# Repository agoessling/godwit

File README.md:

godwit
======

Low-Cost Gliding Computer

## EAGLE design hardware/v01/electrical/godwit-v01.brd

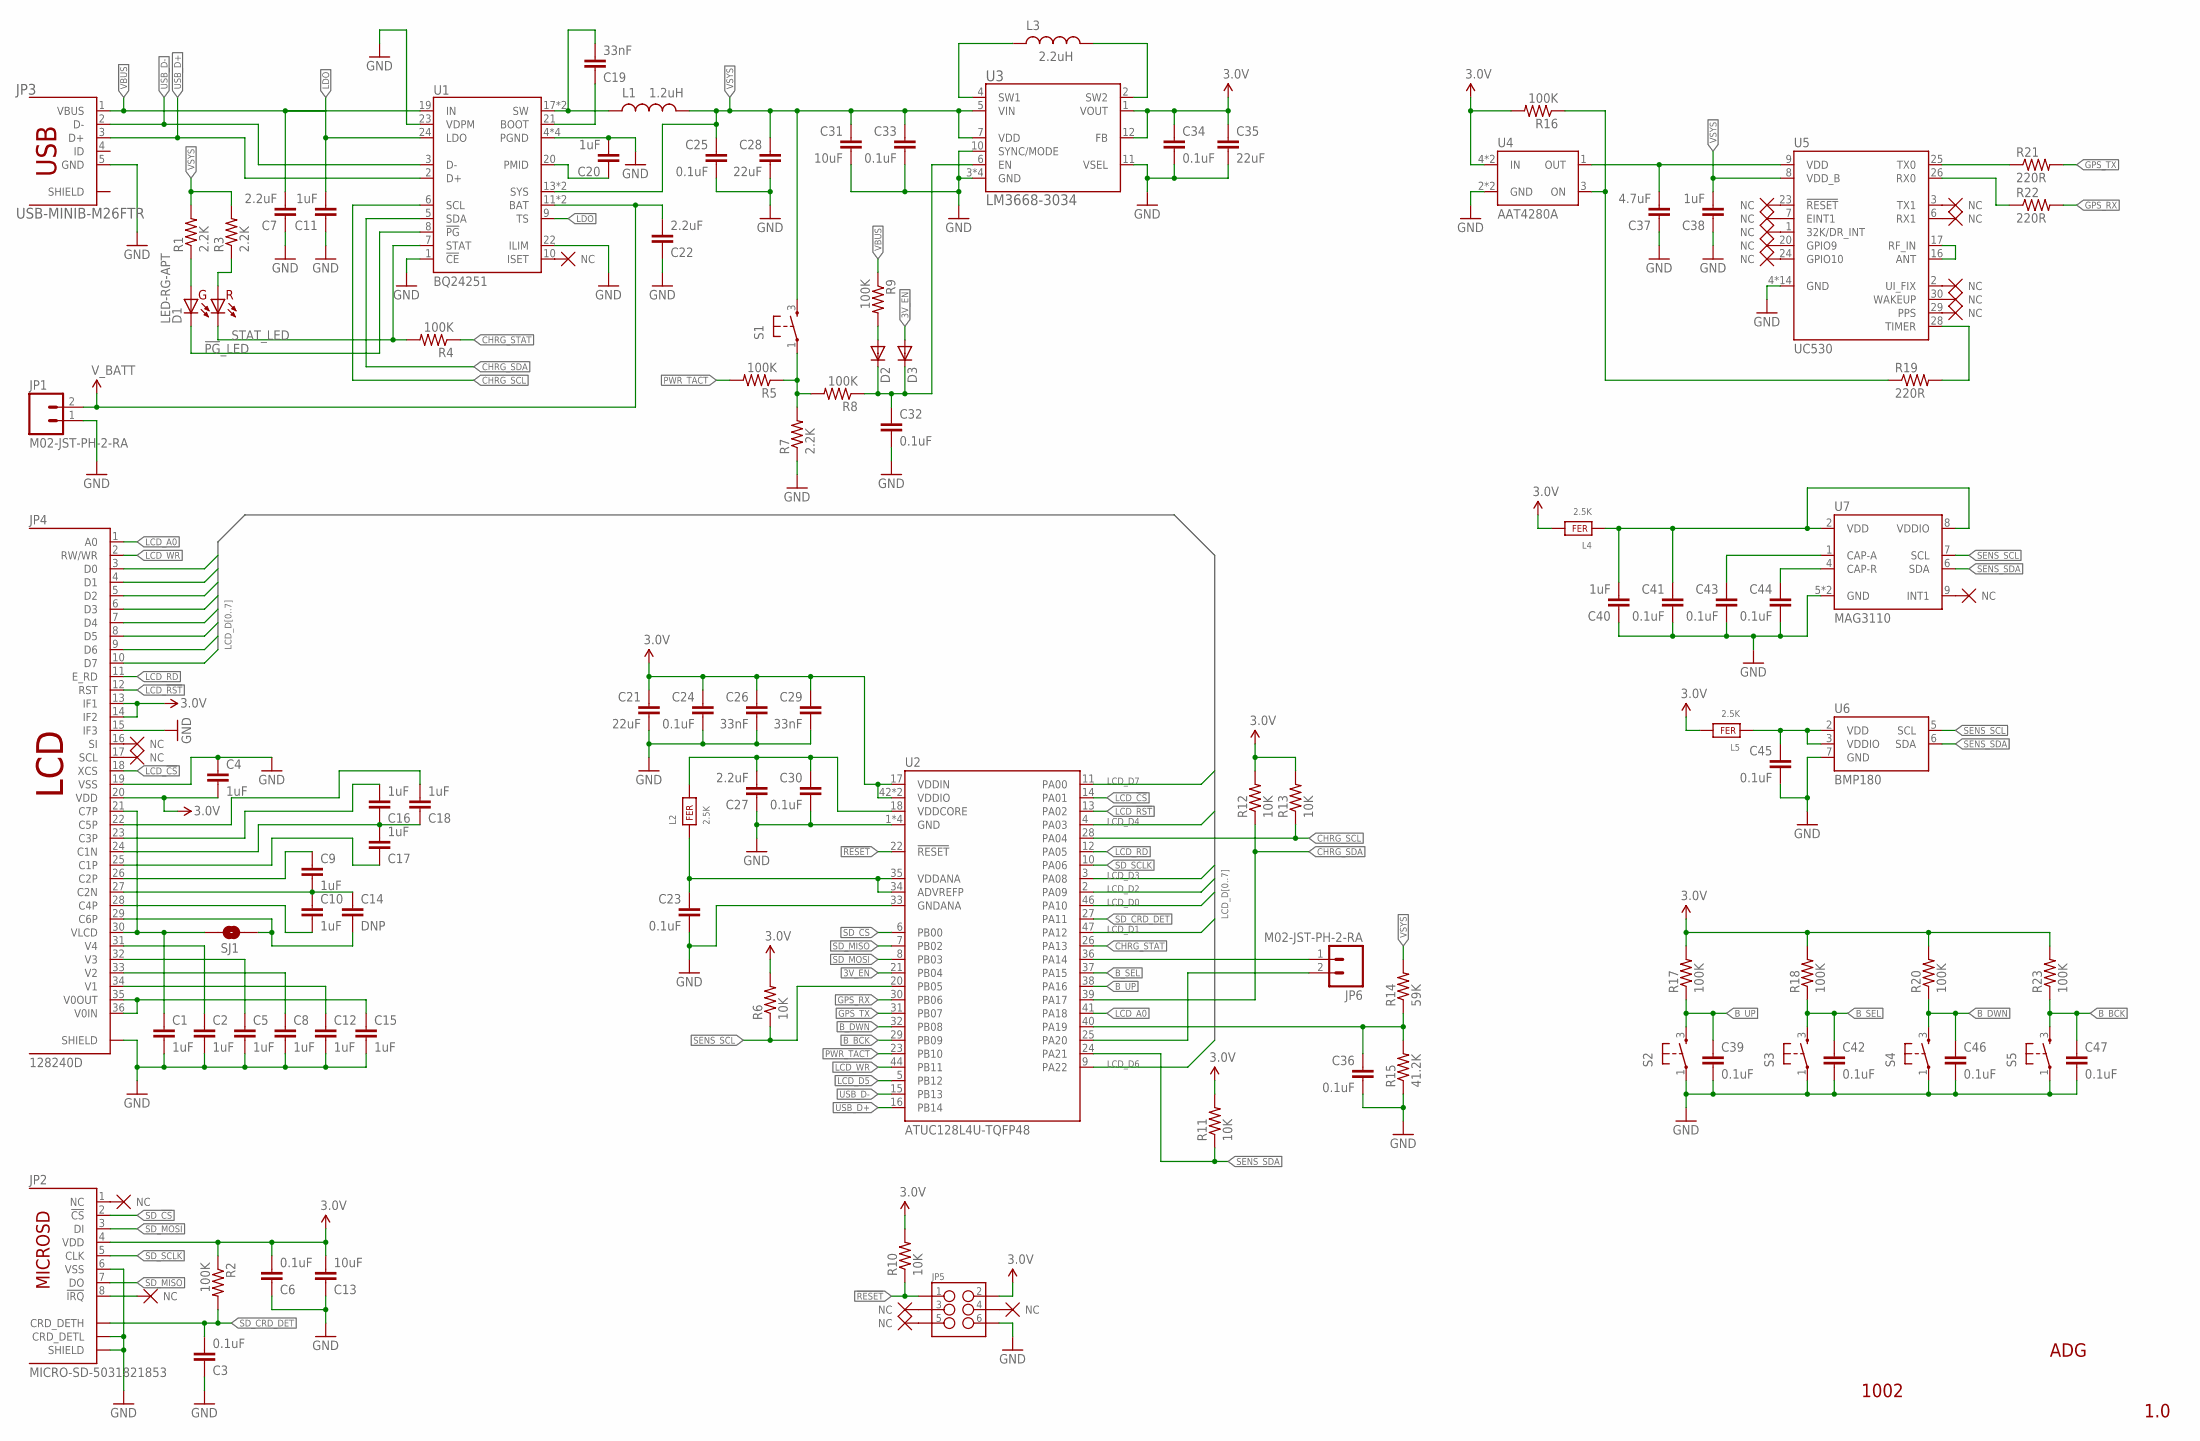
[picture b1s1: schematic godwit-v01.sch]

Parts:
C1, C2, C4, C5, C8, C9, C10, C12, C15, C16, C17, C18: 1uF; C0603
C3, C6, C23, C24, C25, C30, C32, C33, C34, C36, C39, C41, C42, C43, C44, C45, C46, C47: 0.1uF; C0603
C7, C22, C27: 2.2uF; C0603
C11, C20, C38, C40: 1uF; C0603; VOLTAGE >=10V
C13, C31: 10uF; C0805
C14: DNP; C0603
C19: 33nF; C0603; VOLTAGE >15
C21, C28, C35: 22uF; C0805
C26, C29: 33nF; C0603
C37: 4.7uF; C0603; VOLTAGE >=10V
D1: LED-RG-APT; LED-2-1.6X1.25
D2, D3: 1N4148X-TP; SOD523
JP1, JP6: M02-JST-PH-2-RA; JST-PH-2-RA
JP2: MICRO-SD-5031821853; MICROSD-5031821853
JP3: USB-MINIB-M26FTR
JP4: 128240D
JP5: M03X2NO_SILK; 2X3-NS
L1: 1.2uH; SRU5028
L2, L4, L5: 2.5K; 0603
L3: 2.2uH; SRU5028
R1, R3, R7: 2.2K; R0603
R2, R4, R5, R8, R9, R16, R17, R18, R20, R23: 100K; R0603
R6, R10, R11, R12, R13: 10K; R0603
R14: 59K; R0603
R15: 41.2K; R0603
R19, R21, R22: 220R; R0603
S1, S2, S3, S4, S5: FSMRA7JH; FSMRA
SJ1: SOLDERJUMPERNC; SJ_2S
U1: BQ24251; VQFN-24
U2: ATUC128L4U-TQFP48; TQFP48
U3: LM3668-3034; WSON-12
U4: AAT4280A; SOT23-6
U5: UC530
U6: BMP180
U7: MAG3110; DFN-10-2X2

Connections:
3.0V: C4.2, C6.2, C13.2, C21.1, C24.1, C26.1, C29.1, C34.1, C35.1, JP2.4 (VDD), JP4.13 (IF1), JP4.14 (IF2), JP4.20 (VDD), JP5.2, L4.2, L5.2, R2.1, R6.2, R10.2, R11.2, R12.2, R13.2, R16.2, R17.2, R18.2, R20.2, R23.2, U2.17 (VDDIN), U2.42 (VDDIO), U2.48 (VDDIO), U3.1 (VOUT), U3.12 (FB), U4.4 (IN), U4.6 (IN)
3V_EN: D3.A, U2.21 (PB04)
!PG!_LED: D1.4 (CG), U1.8 (!PG!)
!RESET!: JP5.1, R10.1, U2.22 (!RESET!)
B_BCK: C47.1, R23.1, S5.3 (2), U2.29 (PB09)
B_DWN: C46.1, R20.1, S4.3 (2), U2.32 (PB08)
B_SEL: C42.1, R18.1, S3.3 (2), U2.37 (PA15)
B_UP: C39.1, R17.1, S2.3 (2), U2.38 (PA16)
CHRG_SCL: R13.1, U1.6 (SCL), U2.28 (PA04)
CHRG_SDA: R12.1, U1.5 (SDA), U2.39 (PA17)
CHRG_STAT: R4.1, U2.26 (PA13)
GND: C1.2, C2.2, C3.1, C4.1, C5.2, C6.1, C7.1, C8.2, C11.1, C12.2, C13.1, C15.2, C20.2, C21.2, C22.1, C23.2, C24.2, C25.2, C26.2, C27.1, C28.2, C29.2, C30.2, C31.2, C32.2, C33.2, C34.2, C35.2, C36.2, C37.1, C38.1, C39.2, C40.1, C41.2, C42.2, C43.2, C44.2, C45.2, C46.2, C47.2, JP1.1, JP2.6 (VSS), JP2.CRD_DETL, JP2.SHIELD1 (SHIELD), JP2.SHIELD2 (SHIELD), JP2.SHIELD3 (SHIELD), JP2.SHIELD4 (SHIELD), JP2.SHIELD5 (SHIELD), JP3.5 (GND), JP4.15 (IF3), JP4.19 (VSS), JP4.SHIELD1 (SHIELD), JP4.SHIELD2 (SHIELD), JP5.6, R7.1, R15.1, S2.1, S3.1, S4.1, S5.1, U1.1 (!CE!), U1.4 (PGND), U1.15 (PGND), U1.16 (PGND), U1.22 (ILIM), U1.23 (VDPM), U1.PAD (PGND), U2.1 (GND), U2.19 (GND), U2.33 (GNDANA), U2.43 (GND), U2.45 (GND), U3.3 (GND), U3.8 (GND), U3.9 (GND), U3.10 (SYNC/MODE), U3.11 (VSEL), U3.PAD (GND), U4.2 (GND), U4.5 (GND), U5.4 (GND), U5.5 (GND), U5.10 (GND), U5.11 (GND), U5.12 (GND), U5.13 (GND), U5.14 (GND), U5.15 (GND), U5.18 (GND), U5.19 (GND), U5.21 (GND), U5.22 (GND), U5.27 (GND), U5.31 (GND), U6.7 (GND), U7.5 (GND), U7.10 (GND)
GPS_RX: R22.2, U2.30 (PB06)
GPS_TX: R21.2, U2.31 (PB07)
LCD_!CS!: JP4.18 (XCS), U2.14 (PA01)
LCD_!RST!: JP4.12 (RST), U2.13 (PA02)
LCD_A0: JP4.1 (A0), U2.41 (PA18)
LCD_D0: JP4.3 (D0), U2.46 (PA10)
LCD_D1: JP4.4 (D1), U2.47 (PA12)
LCD_D2: JP4.5 (D2), U2.2 (PA09)
LCD_D3: JP4.6 (D3), U2.3 (PA08)
LCD_D4: JP4.7 (D4), U2.4 (PA03)
LCD_D5: JP4.8 (D5), U2.5 (PB12)
LCD_D6: JP4.9 (D6), U2.9 (PA22)
LCD_D7: JP4.10 (D7), U2.11 (PA00)
LCD_RD: JP4.11 (E_RD), U2.12 (PA05)
LCD_WR: JP4.2 (RW/WR), U2.44 (PB11)
LDO: C11.2, U1.9 (TS), U1.24 (LDO)
unnamed: L3.2, U3.2 (SW2)
unnamed: L3.1, U3.4 (SW1)
unnamed: C19.1, U1.21 (BOOT)
unnamed: U5.16 (ANT), U5.17 (RF_IN)
unnamed: C19.2, L1.1, U1.17 (SW), U1.18 (SW)
unnamed: C20.1, U1.20 (PMID)
unnamed: D2.A, R9.2
unnamed: C32.1, D2.C, D3.C, R8.1, U3.6 (EN)
unnamed: D1.3 (AG), R1.1
unnamed: D1.1 (AR), R3.1
unnamed: C37.2, U4.1 (OUT), U5.9 (VDD)
unnamed: R21.1, U5.25 (TX0)
unnamed: R22.1, U5.26 (RX0)
unnamed: R19.2, U5.28 (TIMER)
unnamed: R16.1, R19.1, U4.3 (ON)
unnamed: C9.2, C10.1, C14.1, JP4.27 (C2N)
unnamed: C44.1, U7.4 (CAP-R)
unnamed: C43.1, U7.1 (CAP-A)
unnamed: C9.1, JP4.26 (C2P)
unnamed: C10.2, JP4.28 (C4P)
unnamed: C14.2, JP4.29 (C6P), SJ1.2
unnamed: C16.1, C17.2, C18.1, JP4.24 (C1N)
unnamed: C17.1, JP4.25 (C1P)
unnamed: C16.2, JP4.23 (C3P)
unnamed: C18.2, JP4.22 (C5P)
unnamed: C2.1, JP4.31 (V4)
unnamed: C5.1, JP4.32 (V3)
unnamed: C1.1, JP4.21 (C7P), JP4.30 (VLCD), SJ1.1
unnamed: C8.1, JP4.33 (V2)
unnamed: C12.1, JP4.34 (V1)
unnamed: C15.1, JP4.35 (V0OUT), JP4.36 (V0IN)
unnamed: C36.1, R14.1, R15.2, U2.40 (PA19)
unnamed: JP6.1, U2.36 (PA14)
unnamed: C45.1, L5.1, U6.2 (VDD), U6.3 (VDDIO)
unnamed: JP6.2, U2.25 (PA20)
unnamed: C23.1, L2.1, U2.34 (ADVREFP), U2.35 (VDDANA)
unnamed: C27.2, C30.1, L2.2, U2.18 (VDDCORE)
unnamed: C40.2, C41.1, L4.1, U7.2 (VDD), U7.8 (VDDIO)
unnamed: R5.1, R7.2, R8.2, S1.1
PWR_TACT: R5.2, U2.23 (PB10)
SD_!CS!: JP2.2 (!CS!), U2.6 (PB00)
SD_CRD_DET: C3.2, JP2.CRD_DETH, R2.2, U2.27 (PA11)
SD_MISO: JP2.7 (DO), U2.7 (PB02)
SD_MOSI: JP2.3 (DI), U2.8 (PB03)
SD_SCLK: JP2.5 (CLK), U2.10 (PA06)
SENS_SCL: R6.1, U2.20 (PB05), U6.5 (SCL), U7.7 (SCL)
SENS_SDA: R11.1, U2.24 (PA21), U6.6 (SDA), U7.6 (SDA)
STAT_LED: D1.2 (CR), R4.2, U1.7 (STAT)
USB_D+: JP3.3 (D+), U1.2 (D+), U2.16 (PB14)
USB_D-: JP3.2 (D-), U1.3 (D-), U2.15 (PB13)
VBUS: C7.2, JP3.1 (VBUS), R9.1, U1.19 (IN)
VSYS: C25.1, C28.1, C31.1, C33.1, C38.2, L1.2, R1.2, R3.2, R14.2, S1.3 (2), U1.13 (SYS), U1.14 (SYS), U3.5 (VIN), U3.7 (VDD), U5.8 (VDD_B)
V_BATT: C22.2, JP1.2, U1.11 (BAT), U1.12 (BAT)

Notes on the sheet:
ADG
1002
1.0

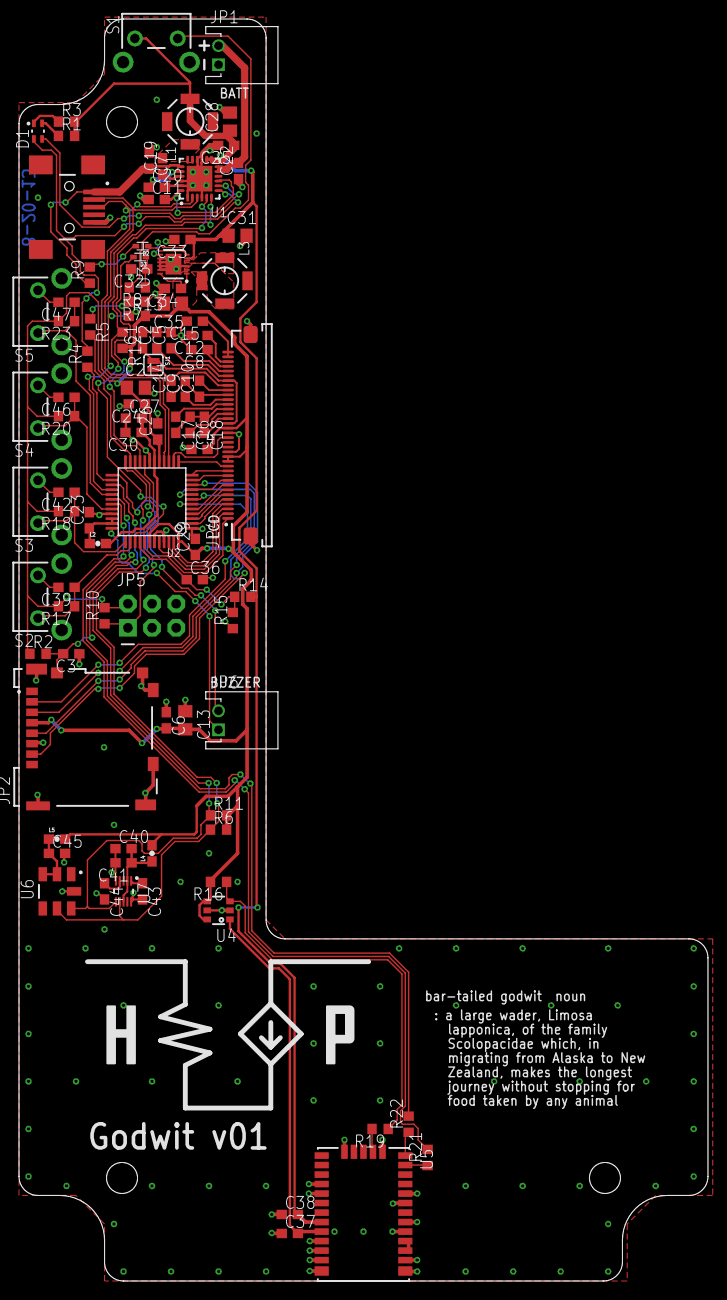
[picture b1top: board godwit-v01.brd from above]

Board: 2 copper layers, 72.5 x 132.8 mm, 98 parts (0 on the bottom side), 81 nets.

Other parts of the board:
U$21: LOGO_MED_SLK

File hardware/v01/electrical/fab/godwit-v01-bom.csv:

Qty,Value,Device,Package,Parts,VENDOR,VENDOR_PN
1,M03x2,M03X2NO_SILK,2X3-NS,JP5,DIGI-KEY,952-2121-ND
18,0.1uF,C-EUC0603,C0603,"C3, C6, C23, C24, C25, C30, C32, C33, C34, C36, C39, C41, C42, C43, C44, C45, C46, C47",DIGI-KEY,1276-1005-1-ND
10,100K,R-US_R0603,R0603,"R2, R4, R5, R8, R9, R16, R17, R18, R20, R23",DIGI-KEY,1276-5110-1-ND
5,10K,R-US_R0603,R0603,"R6, R10, R11, R12, R13",DIGI-KEY,1276-5086-1-ND
2,10uF,C-EUC0805,C0805,"C13, C31",DIGI-KEY,490-6470-1-ND
1,128240D,128240D,128240D,JP4,MOUSER,758-SEA8056-36
2,1N4148X-TP,DIODESOD523,SOD523,"D2, D3",DIGI-KEY,1N4148XTPMSCT-ND
16,1uF,C-EUC0603,C0603,"C1, C2, C4, C5, C8, C9, C10, C12, C15, C16, C17, C18, C11, C20, C38, C40",DIGI-KEY,587-1248-1-ND
1,1.2uH,INDUCTOR-SRU5028,SRU5028,L1,DIGI-KEY,SRU5028-1R2YCT-ND
3,2.2K,R-US_R0603,R0603,"R1, R3, R7",DIGI-KEY,1276-5070-1-ND
3,2.2uF,C-EUC0603,C0603,"C7, C22, C27",DIGI-KEY,445-5167-1-ND
1,2.2uH,INDUCTOR-SRU5028,SRU5028,L3,DiGI-KEY,SRU5028-2R2YCT-ND
3,2.5K,FERRITE-BEAD-0603,603,"L2, L4, L5",DIGI-KEY,587-1893-1-ND
3,220R,R-US_R0603,R0603,"R19, R21, R22",DIGI-KEY,1276-5046-1-ND
3,22uF,C-EUC0805,C0805,"C21, C28, C35",DIGI-KEY,587-1305-1-ND
3,33nF,C-EUC0603,C0603,"C19, C26, C29",DIGI-KEY,1276-2042-1-ND
1,4.7uF,C-EUC0603,C0603,C37,DIGI-KEY,490-3297-1-ND
1,41.2K,R-US_R0603,R0603,R15,DiGI-KEY,1276-4801-1-ND
1,59K,R-US_R0603,R0603,R14,DiGI-KEY,1276-4818-1-ND
1,AAT4280A,AAT4280A,SOT23-6,U4,DIGI-KEY,863-1486-1-ND
1,ATUC128L4U-TQFP48,ATUC128L4U-TQFP48,TQFP48,U2,DIGI-KEY,ATUC128L4U-AUT-ND
1,BMP180,BMP180,BMP180,U6,DIGI-KEY,828-1027-1-ND
1,BQ24251,BQ24251,VQFN-24,U1,DIGI-KEY,296-36444-1-ND
5,FSMRA7JH,TAC_SWITCH-FSMRA,FSMRA,"S1, S2, S3, S4, S5",DIGI-KEY,450-1661-ND
1,LED-RG-APT,LED-RG-APT,LED-2-1.6X1.25,D1,DIGI-KEY,754-1146-1-ND
1,LM3668-3034,LM3668-3034,WSON-12,U3,DIGI-KEY,LM3668SD-3034/NOPBCT-ND
2,M02-JST-PH-2-RA,M02-JST-PH-2-RA,JST-PH-2-RA,"JP1, JP6",DIGI-KEY,455-1719-ND
1,MAG3110,MAG3110,DFN-10-2X2,U7,DIGI-KEY,MAG3110FCR1CT-ND
1,MICRO-SD-5031821853,MICRO-SD-5031821853,MICROSD-5031821853,JP2,DIGI-KEY,WM9750CT-ND
1,UC530,UC530,UC530,U5,MOUSER,916-UC530
1,USB-MINIB-M26FTR,USB-MINIB-M26FTR,USB-MINIB-M26FTR,JP3,DIGI-KEY,ED2992CT-ND

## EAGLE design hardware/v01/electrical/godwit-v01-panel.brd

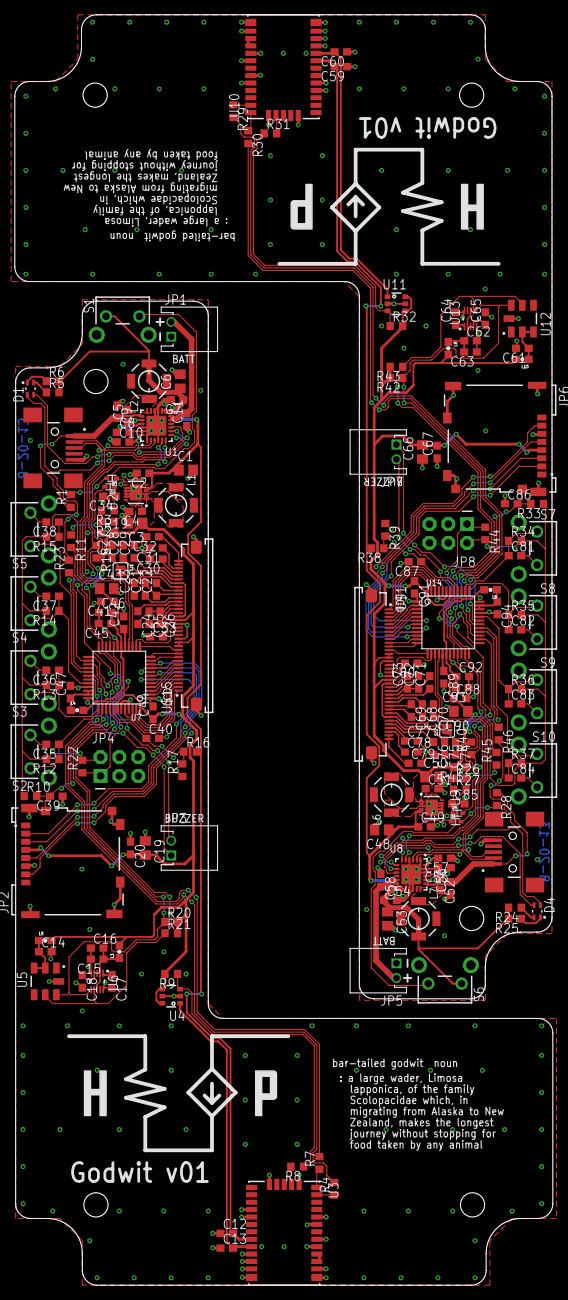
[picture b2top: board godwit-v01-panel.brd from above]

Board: 2 copper layers, 72.6 x 171.4 mm, 196 parts (0 on the bottom side), 162 nets.

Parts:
C1, C19, C48, C66: 10uF; C0805
C2, C4, C7, C14, C15, C17, C18, C20, C34, C35, C36, C37, C38, C39, C40, C41, C45, C47, C49, C51, C54, C61, C62, C64, C65, C67, C81, C82, C83, C84, C85, C86, C87, C88, C92, C94: 0.1uF; C0603
C3, C6, C43, C50, C53, C90: 22uF; C0805
C5, C42, C44, C52, C89, C91: 33nF; C0603
C8, C10, C12, C16, C21, C22, C24, C25, C26, C27, C28, C29, C30, C31, C32, C33, C55, C57, C59, C63, C68, C69, C71, C72, C73, C74, C75, C76, C77, C78, C79, C80: 1uF; C0603
C9, C11, C46, C56, C58, C93: 2.2uF; C0603
C13, C60: 4.7uF; C0603
C23, C70: DNP; C0603
D1, D4: LED-RG-APT; LED-2-1.6X1.25
D2, D3, D5, D6: SOD523
J1, J2: USB-MINIB-M26FTR
JP1, JP3, JP5, JP7: M02-JST-PH-2-RA; JST-PH-2-RA
JP2, JP6: MICRO-SD-5031821853; MICROSD-5031821853
JP4, JP8: 2X3-NS
L1, L6: 2.2uH; SRU5028
L2, L7: 1uH; SRU5028
L3, L4, L5, L8, L9, L10: 2.5K; 0603
R1, R3, R9, R10, R11, R12, R13, R14, R15, R23, R27, R28, R32, R33, R34, R35, R36, R37, R45, R46: 100K; R0603
R2, R5, R6, R24, R25, R26: 2.2K; R0603
R4, R7, R8, R29, R30, R31: 220R; R0603
R16, R38: 59K; R0603
R17, R39: 41.2K; R0603
R18, R19, R20, R21, R22, R40, R41, R42, R43, R44: 10K; R0603
S1, S2, S3, S4, S5, S6, S7, S8, S9, S10: FSMRA
SJ1, SJ2: SOLDERJUMPERNC; SJ_2S
U1, U8: BQ24251; VQFN-24
U2, U9: LM3668-3034; WSON-12
U3, U10: UC530
U4, U11: AAT4280A; SOT23-6
U5, U12: BMP180
U6, U13: MAG3110; DFN-10-2X2
U7, U14: ATUCL4U-TQFP48; TQFP48
U$1, U$15: 128240D
U$2, U$21: LOGO_MED_SLK

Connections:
3.0V: C3.1, C4.1, C19.2, C20.2, C33.2, C41.1, C42.1, C43.1, C44.1, JP2.4, JP4.2, L3.2, L5.2, R9.2, R10.1, R12.2, R13.2, R14.2, R15.2, R18.2, R19.2, R20.2, R21.2, R22.2, U2.1, U2.12, U4.4, U4.6, U7.17, U7.42, U7.48, U$15.13, U$15.14, U$15.20
3.0V1: C50.1, C51.1, C66.2, C67.2, C80.2, C88.1, C89.1, C90.1, C91.1, JP6.4, JP8.2, L9.2, L10.2, R32.2, R33.1, R34.2, R35.2, R36.2, R37.2, R40.2, R41.2, R42.2, R43.2, R44.2, U9.1, U9.12, U11.4, U11.6, U14.17, U14.42, U14.48, U$1.13, U$1.14, U$1.20
3V_EN: D2.A, U7.21
3V_EN1: D5.A, U14.21
!PG!_LED: D1.4, U1.8
!PG!_LED1: D4.4, U8.8
!RESET!: JP4.1, R22.1, U7.22
!RESET!1: JP8.1, R44.1, U14.22
B_BCK: C38.1, R15.1, S5.3, U7.29
B_BCK1: C84.1, R37.1, S10.3, U14.29
B_DWN: C37.1, R14.1, S4.3, U7.32
B_DWN1: C83.1, R36.1, S9.3, U14.32
B_SEL: C36.1, R13.1, S3.3, U7.37
B_SEL1: C82.1, R35.1, S8.3, U14.37
B_UP: C35.1, R12.1, S2.3, U7.38
B_UP1: C81.1, R34.1, S7.3, U14.38
CHRG_SCL: R19.1, U1.6, U7.28
CHRG_SCL1: R41.1, U8.6, U14.28
CHRG_SDA: R18.1, U1.5, U7.39
CHRG_SDA1: R40.1, U8.5, U14.39
CHRG_STAT: R23.1, U7.26
CHRG_STAT1: R46.1, U14.26
GND: C1.2, C2.2, C3.2, C4.2, C6.2, C7.2, C8.2, C9.1, C10.1, C11.1, C12.1, C13.1, C14.2, C15.2, C16.1, C17.2, C18.2, C19.1, C20.1, C27.2, C28.2, C29.2, C30.2, C31.2, C32.2, C33.1, C34.2, C35.2, C36.2, C37.2, C38.2, C39.1, C40.2, C41.2, C42.2, C43.2, C44.2, C45.2, C46.1, C47.2, J1.5, JP1.1, JP2.6, JP2.CRD_DETL, JP2.SHIELD1, JP2.SHIELD2, JP2.SHIELD3, JP2.SHIELD4, JP2.SHIELD5, JP4.6, R2.1, R17.1, S2.1, S3.1, S4.1, S5.1, U1.1, U1.4, U1.15, U1.16, U1.22, U1.23, U1.PAD, U2.3, U2.8, U2.9, U2.10, U2.11, U2.PAD, U3.4, U3.5, U3.10, U3.11, U3.12, U3.13, U3.14, U3.15, U3.18, U3.19, U3.21, U3.22, U3.27, U3.31, U4.2, U4.5, U5.7, U6.5, U6.10, U7.1, U7.19, U7.33, U7.43, U7.45, U$15.15, U$15.19, U$15.SHIELD1, U$15.SHIELD2
GND1: C48.2, C49.2, C50.2, C51.2, C53.2, C54.2, C55.2, C56.1, C57.1, C58.1, C59.1, C60.1, C61.2, C62.2, C63.1, C64.2, C65.2, C66.1, C67.1, C74.2, C75.2, C76.2, C77.2, C78.2, C79.2, C80.1, C81.2, C82.2, C83.2, C84.2, C85.2, C86.1, C87.2, C88.2, C89.2, C90.2, C91.2, C92.2, C93.1, C94.2, J2.5, JP5.1, JP6.6, JP6.CRD_DETL, JP6.SHIELD1, JP6.SHIELD2, JP6.SHIELD3, JP6.SHIELD4, JP6.SHIELD5, JP8.6, R26.1, R39.1, S7.1, S8.1, S9.1, S10.1, U8.1, U8.4, U8.15, U8.16, U8.22, U8.23, U8.PAD, U9.3, U9.8, U9.9, U9.10, U9.11, U9.PAD, U10.4, U10.5, U10.10, U10.11, U10.12, U10.13, U10.14, U10.15, U10.18, U10.19, U10.21, U10.22, U10.27, U10.31, U11.2, U11.5, U12.7, U13.5, U13.10, U14.1, U14.19, U14.33, U14.43, U14.45, U$1.15, U$1.19, U$1.SHIELD1, U$1.SHIELD2
GPS_RX: R7.2, U7.30
GPS_RX1: R30.2, U14.30
GPS_TX: R4.2, U7.31
GPS_TX1: R29.2, U14.31
LCD_!CS!: U7.14, U$15.18
LCD_!CS!1: U14.14, U$1.18
LCD_!RST!: U7.13, U$15.12
LCD_!RST!1: U14.13, U$1.12
LCD_A0: U7.41, U$15.1
LCD_A1: U14.41, U$1.1
LCD_D0: U7.46, U$15.3
LCD_D1: U7.47, U$15.4
LCD_D2: U7.2, U$15.5
LCD_D3: U7.3, U$15.6
LCD_D4: U7.4, U$15.7
LCD_D5: U7.5, U$15.8
LCD_D6: U7.9, U$15.9
LCD_D7: U7.11, U$15.10
LCD_D8: U14.11, U$1.10
LCD_D9: U14.9, U$1.9
LCD_D10: U14.5, U$1.8
LCD_D11: U14.4, U$1.7
LCD_D12: U14.3, U$1.6
LCD_D13: U14.47, U$1.4
LCD_D14: U14.46, U$1.3
LCD_D15: U14.2, U$1.5
LCD_RD: U7.12, U$15.11
LCD_RD1: U14.12, U$1.11
LCD_WR: U7.44, U$15.2
LCD_WR1: U14.44, U$1.2
LDO: C10.2, U1.9, U1.24
LDO1: C57.2, U8.9, U8.24
unnamed: L1.2, U2.2
unnamed: L1.1, U2.4
unnamed: C5.1, U1.21
unnamed: U3.16, U3.17
unnamed: C5.2, L2.1, U1.17, U1.18
unnamed: C8.1, U1.20
unnamed: D3.A, R1.2
unnamed: C34.1, D2.C, D3.C, R3.1, U2.6
unnamed: D1.3, R5.1
unnamed: D1.1, R6.1
unnamed: C13.2, U3.9, U4.1
unnamed: R4.1, U3.25
unnamed: R7.1, U3.26
unnamed: R8.2, U3.28
unnamed: R8.1, R9.1, U4.3
unnamed: C21.2, C22.1, C23.1, U$15.27
unnamed: C18.1, U6.4
unnamed: C17.1, U6.1
unnamed: C21.1, U$15.26
unnamed: C22.2, U$15.28
unnamed: C23.2, SJ1.2, U$15.29
unnamed: C24.2, C25.1, C26.1, U$15.24
unnamed: C24.1, U$15.25
unnamed: C25.2, U$15.23
unnamed: C26.2, U$15.22
unnamed: C28.1, U$15.31
unnamed: C29.1, U$15.32
unnamed: C27.1, SJ1.1, U$15.21, U$15.30
unnamed: C30.1, U$15.33
unnamed: C31.1, U$15.34
unnamed: C32.1, U$15.35, U$15.36
unnamed: C40.1, R16.1, R17.2, U7.40
unnamed: JP3.1, U7.36
unnamed: C14.1, L5.1, U5.2, U5.3
unnamed: JP3.2, U7.25
unnamed: C47.1, L4.1, U7.34, U7.35
unnamed: C45.1, C46.2, L4.2, U7.18
unnamed: C15.1, C16.2, L3.1, U6.2, U6.8
unnamed: L6.2, U9.2
unnamed: L6.1, U9.4
unnamed: C52.1, U8.21
unnamed: C52.2, L7.1, U8.17, U8.18
unnamed: C55.1, U8.20
unnamed: D4.3, R24.1
unnamed: D4.1, R25.1
unnamed: D6.A, R28.2
unnamed: C85.1, D5.C, D6.C, R27.1, U9.6
unnamed: U10.16, U10.17
unnamed: C60.2, U10.9, U11.1
unnamed: R29.1, U10.25
unnamed: R30.1, U10.26
unnamed: R31.2, U10.28
unnamed: R31.1, R32.1, U11.3
unnamed: C65.1, U13.4
unnamed: C64.1, U13.1
unnamed: R2.2, R3.2, R11.1, S1.1
unnamed: C68.2, C69.1, C70.1, U$1.27
unnamed: C68.1, U$1.26
unnamed: C69.2, U$1.28
unnamed: C70.2, SJ2.2, U$1.29
unnamed: C71.2, C72.1, C73.1, U$1.24
unnamed: C71.1, U$1.25
unnamed: C72.2, U$1.23
unnamed: C73.2, U$1.22
unnamed: C74.1, SJ2.1, U$1.21, U$1.30
unnamed: C75.1, U$1.31
unnamed: C76.1, U$1.32
unnamed: C77.1, U$1.33
unnamed: C78.1, U$1.34
unnamed: C79.1, U$1.35, U$1.36
unnamed: C87.1, R38.1, R39.2, U14.40
unnamed: JP7.1, U14.36
unnamed: JP7.2, U14.25
unnamed: C92.1, C93.2, L8.2, U14.18
unnamed: C94.1, L8.1, U14.34, U14.35
unnamed: C61.1, L10.1, U12.2, U12.3
unnamed: C62.1, C63.2, L9.1, U13.2, U13.8
unnamed: R26.2, R27.2, R45.1, S6.1
PWR_TACT: R11.2, U7.23
PWR_TACT1: R45.2, U14.23
SD_!CS!: JP2.2, U7.6
SD_!CS!1: JP6.2, U14.6
SD_CRD_DET: C39.2, JP2.CRD_DETH, R10.2, U7.27
SD_CRD_DET1: C86.2, JP6.CRD_DETH, R33.2, U14.27
SD_MISO: JP2.7, U7.7
SD_MISO1: JP6.7, U14.7
SD_MOSI: JP2.3, U7.8
SD_MOSI1: JP6.3, U14.8
SD_SCLK: JP2.5, U7.10
SD_SCLK1: JP6.5, U14.10
SENS_SCL: R21.1, U5.5, U6.7, U7.20
SENS_SCL1: R43.1, U12.5, U13.7, U14.20
SENS_SDA: R20.1, U5.6, U6.6, U7.24
SENS_SDA1: R42.1, U12.6, U13.6, U14.24
STAT_LED: D1.2, R23.2, U1.7
STAT_LED1: D4.2, R46.2, U8.7
USB_D+: J1.3, U1.2, U7.16
USB_D+1: J2.3, U8.2, U14.16
USB_D-: J1.2, U1.3, U7.15
USB_D-1: J2.2, U8.3, U14.15
VBUS: C9.2, J1.1, R1.1, U1.19
VBUS1: C56.2, J2.1, R28.1, U8.19
VSYS: C1.1, C2.1, C6.1, C7.1, C12.2, L2.2, R5.2, R6.2, R16.2, S1.3, U1.13, U1.14, U2.5, U2.7, U3.8
VSYS1: C48.1, C49.1, C53.1, C54.1, C59.2, L7.2, R24.2, R25.2, R38.2, S6.3, U8.13, U8.14, U9.5, U9.7, U10.8
V_BATT: C11.2, JP1.2, U1.11, U1.12
V_BATT1: C58.2, JP5.2, U8.11, U8.12

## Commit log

2013-08-05 Added ignore for eagle backup files.
2013-08-05 Genesis
2013-08-06 Moved directory structure.
2013-08-06 rearranged and added circuits
2013-08-06 removed duplicate pdfs
2013-08-07 Added sensing circuitry.
2013-08-08 Added SD card circuit.
2013-08-08 Added LCD and uC to circuit
2013-08-10 Added LCD signals and EXTINT.
2013-08-17 Started ADC input.
2013-08-19 Finished first draft schematic and layout.
2013-08-20 Spun sd card right way and rerouted...
2013-08-20 Finished EagleUp
2013-08-21 Added current limiting resistors and finalized v01 design.
2013-08-21 panelized and gerbered.
2013-08-22 Prepared Fab documents, and sent off v01.
2013-08-22 Started to add BOM.
2013-08-22 Finished BOM
2013-08-23 added to BOM
2013-08-23 Purchased from BOM.
2013-08-28 Changed sketchup assembly
2013-09-03 Started st7529 library
2013-09-03 Added board specific file for st7529.
2013-09-03 Added LCD init parameters
2013-09-03 eagle project info
2013-09-03 started to write text display.
2013-09-26 Added text display function and 5x7 font header.
2013-09-26 Added Basic Atmel Studio Project
2013-10-03 Added GPS Support
2013-10-03 Cleaned up main.c a bit.
2013-10-07 Wrote Mag and Pressure Support.
    Setup serial dma support for pressure and then mag.
2013-10-08 Added GPS-Synced Tick Interrupt
2013-10-15 Setup Buzzer PWM
2015-10-13 Add beginnings of custom library.

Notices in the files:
parts and their libraries:
SparkFun-Aesthetics: Licensing: CC v3.0 Share-Alike You are welcome to use this library for commercial purposes.
